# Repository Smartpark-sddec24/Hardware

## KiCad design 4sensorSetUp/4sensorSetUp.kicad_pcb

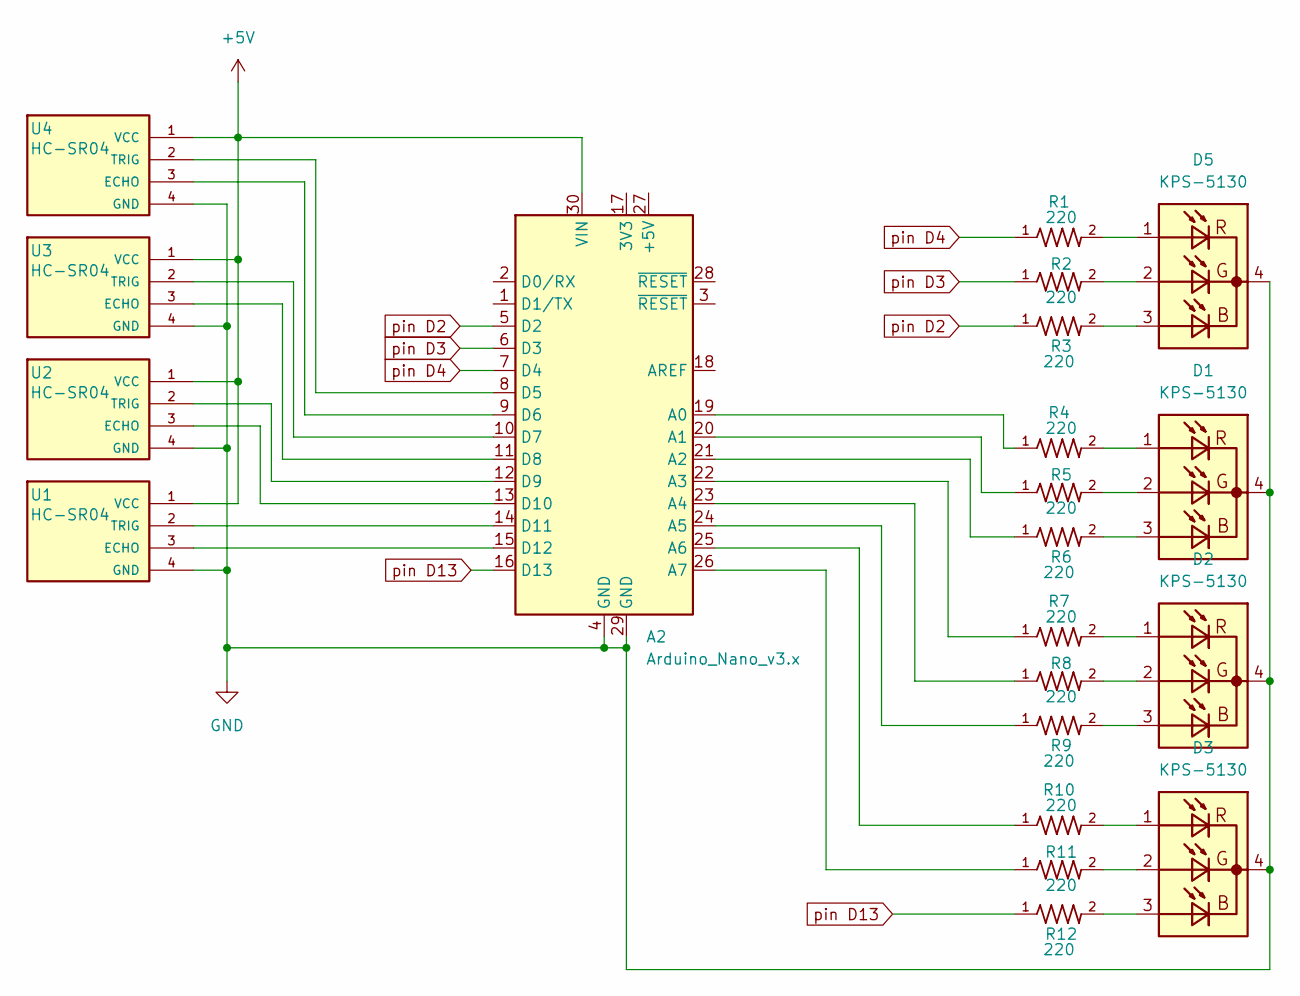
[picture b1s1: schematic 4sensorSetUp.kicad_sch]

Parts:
A2: Arduino_Nano_v3.x; Arduino_Nano
D1, D2, D3, D5: KPS-5130; Kingbright_KPS-5130
R1, R2, R3, R4, R5, R6, R7, R8, R9, R10, R11, R12: 220; RESC1005X35N_3-1676480-4; Voltage_Rating 50 V; Tolerance 1%
U1, U2, U3, U4: HC-SR04; XCVR_HC-SR04

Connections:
+5V: A2.30 (VIN), U1.1 (VCC), U2.1 (VCC), U3.1 (VCC), U4.1 (VCC)
GND: A2.4 (GND), A2.29 (GND), D1.4 (C), D2.4 (C), D3.4 (C), D5.4 (C), U1.4 (GND), U2.4 (GND), U3.4 (GND), U4.4 (GND)
unnamed: A2.19 (A0), R4.1
unnamed: A2.20 (A1), R5.1
unnamed: A2.21 (A2), R6.1
unnamed: A2.22 (A3), R7.1
unnamed: A2.23 (A4), R8.1
unnamed: A2.24 (A5), R9.1
unnamed: A2.25 (A6), R10.1
unnamed: A2.26 (A7), R11.1
unnamed: A2.8 (D5), U4.2 (TRIG)
unnamed: A2.9 (D6), U4.3 (ECHO)
unnamed: A2.10 (D7), U3.2 (TRIG)
unnamed: A2.11 (D8), U3.3 (ECHO)
unnamed: A2.12 (D9), U2.2 (TRIG)
unnamed: A2.13 (D10), U2.3 (ECHO)
unnamed: A2.14 (D11), U1.2 (TRIG)
unnamed: A2.15 (D12), U1.3 (ECHO)
unnamed: D1.3 (AB), R6.2
unnamed: D1.2 (AG), R5.2
unnamed: D1.1 (AR), R4.2
unnamed: D2.3 (AB), R9.2
unnamed: D2.2 (AG), R8.2
unnamed: D2.1 (AR), R7.2
unnamed: D3.3 (AB), R12.2
unnamed: D3.2 (AG), R11.2
unnamed: D3.1 (AR), R10.2
unnamed: D5.3 (AB), R3.2
unnamed: D5.2 (AG), R2.2
unnamed: D5.1 (AR), R1.2
pin D2: A2.5 (D2), R3.1
pin D3: A2.6 (D3), R2.1
pin D4: A2.7 (D4), R1.1
pin D13: A2.16 (D13), R12.1

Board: 2 copper layers, 21 parts (0 on the bottom side), 34 nets, no tracks yet.

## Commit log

2024-10-07 Initial commit: Adds main file, wifi .h and .cpp files, commented sensor array .h file, and an empty sensor array .cpp file
2024-10-07 Uncommented SensorArray.h code and added a private array of DistanceSensors
2024-10-09 Deleted SensorArray files and added the sensor code to the main file. Subject to revision
2024-10-11 Commiting updated versions of the sensor array library, filled in one the SensorArray constructor in the .cpp file
2024-10-11 Tested final and it's working! Added a timing system so that the system is not constantly outputting data to the serial monitor, but it's not fully functional though it doesn't break anything
2024-10-11 Updated sensors to descend pin order, i.e. Sensor 1 uses pins 11 and 12, etc. Included HttpClient.h
2024-10-11 Create Schematic and PCB
2024-10-11 Schematic and PCB design
2024-10-11 Minor spelling corrections
2024-10-11 Unknown changes, but code still compiles
2024-10-15 Commented loop code, began coding for http requests
2024-10-15 Removed HttpClient.h include
2024-10-15 Commented entire .ino file, modified sensorArray.h and its .cpp files to utilize an arrray of DistanceSensors. NOTE: Try creating pinArray and sensorArray structs to solve compile issue
2024-10-16 Still working on SensorArray Library, no serious changes. Errors about DistanceSensor constructor
2024-10-18 Successfully sent a GET request
2024-10-18 continued updating sensorArray.h and .cpp files to create an array of distance sensors, still not working, lol
2024-10-20 I HAVE COMPILATIONgit add .git add . I removed the constructor definition from SensorArray.cpp
2024-10-20 back to not DistanceSensor constructor error
2024-10-21 Rewrote the SensorArray.h and .cpp files to set a spot's status based on a measured distance and get a spot's current status
2024-10-21 Deleted old sensor array library code
2024-10-22 Commented some print statements to clarify serial monitor output
2024-10-22 deleted print statements
2024-10-22 Add files via upload
    updated the PCB and schematic design to include the RGB LED
2024-10-22 Create PCB setup Kicad
2024-10-23 Added a comment to SensorArray.h
2024-10-23 Second commit attempt: added pcb design, deleted empty pcb file
2024-10-23 Added LED code to the main file
2024-10-25 added the post request to the file
2024-10-25 added functions for get,post, and put
2024-10-25 added distance sensor array and organized the loop to have a for loop
2024-10-28 updated wifiConnection.reconnect() to attempt a reconnection three times after which it will reset the system
2024-10-28 Minor formatting changes in WifiConnection.cpp
2024-10-28 Messed with the LED branch to have a setColor function and tried testing 2 LEDs in the loop
2024-10-29 Began documentation of WiFi library by expanding some of the method descriptions in WifiConnection.h and removed some unnecessary comments and/or code lines throughout the library
2024-10-30 Made extensive documentation updates and TODO comments in the SensorArray.h file in preparation for a rewrite. Also commented that the PUT request in the main file is unsupported in the server API, s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
2024-11-01 Got LED stuff working for 2 at once
2024-11-01 made the trig and echo arrays and added a setup function to the sensory array file
2024-11-04 organized the code and added for loop for testing
2024-11-04 Moved the LED functions to the sensor arry lib and moved the http functions to the wifi lib. organized/ consolidated the code
2024-11-06 added the pin assignments for 4 leds
2024-11-06 Added comments to new SensorArray methods
2024-11-06 Added comments to WifiConnection.h to define the POST request and created two TODOs: one to parse the response body of the request, another to possible change its return type for easier processing
2024-11-11 Found code to enable and use interrupts on the board. Verification in progress
2024-11-11 Commented out deadly interrupt code. More research will be conducted on how to properly implement interrupts
2024-11-14 Attempted to add a new library to use interrupts but there are errors to work out
2024-11-15 Added a sketch that reads the MAC address of a new board for registration with the university WiFi network
2024-11-15 Interrupts are hesitantly implemented. There are a few details to work out, but theoretically, we are back on track
2024-11-18 Commented out 'Timer overflow' print statement inside interrupt handler in loop
2024-11-18 Removed interval wait time for wifiInfo() due to new interrupt inclusion. Slightly modified wifi.begin() to check conneciton status after the 10 second delay to check for actual connecttion creation
2024-11-18 Added a 10 second delay after a reconnect attempt to account for connection creation. This will need to be balanced with the interrupt system
2024-11-19 Added a disable interrupt flag in WifiConnection library, added flag handler to main file loop function
2024-11-19 adjusted the void loop to test the software team server. adjusted the updateSpot post request to match the software server.
2024-11-20 Updated wifi connection system to handle a Disconnected status on startup. After three attempts with a Disconnected status, the system will do an automatic reset
2024-11-20 Post request working with software server
2024-11-21 Official code sequence started. Numerous changes to main file, sensor array, and wifi connection libraries. Biggest changes are a rewrite of the measurement function to average multiple measurements 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
2024-11-22 cleaned up files
2024-11-22 Deleted some comments
2024-11-22 Added MAC address functionality
2024-11-22 wrote in the loop function how LEDS to light up according to the sensor values
2024-11-22 cleaned up the loop function
2024-12-03 Placed initial TODO comments for updating the average measurement system
2024-12-04 added an initialize GET request, began hardware-server testing
2024-12-04 Updated minimum distance for vehicle detection
2024-12-06 Adjusted the code to send and recieve an array for the post request
2024-12-07 Post request updated to send id and occupied arrays via a request body. Removed some testing print statements. Updated setup function to ensure the spot ids are retrieved from the server.
2024-12-07 FINAL HARDWARE CODE PUSH. To be merged with main branch for final demo. Necessary print statements will be added in main for final touches
2024-12-08 miinor spacing changes
2024-12-08 Merged sensorArrayBrach into main, inlcuded dynamic MAC address retrieval, removed TODO comments in SensorArray.h. The mac argument of the post requst may cause an incorrect data type error, this nee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
2024-12-09 Added dynamic mac retreival from the board on set up
2024-12-09 changed the sprintf statement in the get request
2024-12-12 we changed how is_reserved is formatted so it actually stores the int array rather than an int pointer also commented out some prints and delays
